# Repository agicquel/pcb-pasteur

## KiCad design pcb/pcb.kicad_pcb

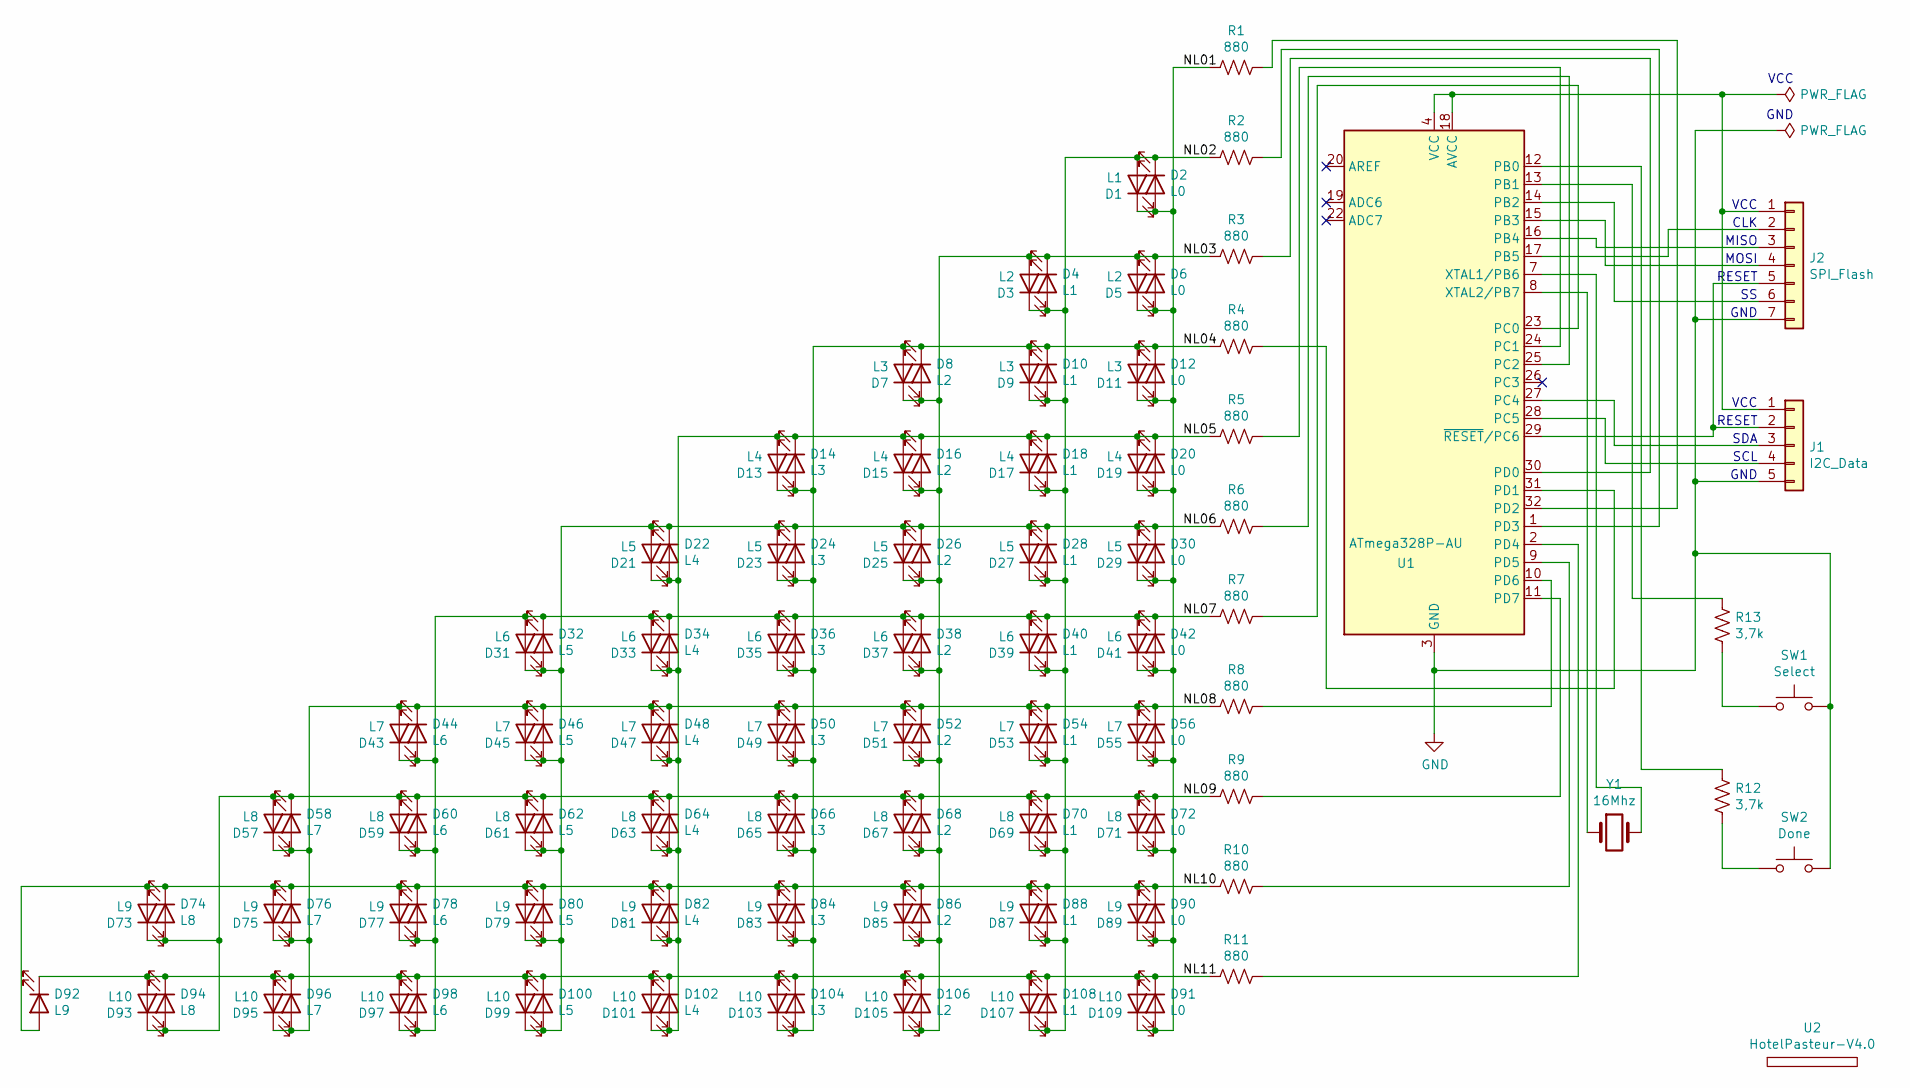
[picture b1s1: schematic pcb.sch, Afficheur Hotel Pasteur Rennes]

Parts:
D1, D4, D10, D18, D28, D40, D54, D70, D88, D108: L1; LED_0603_1608Metric_smallfont
D2, D6, D12, D20, D30, D42, D56, D72, D90, D91: L0; LED_0603_1608Metric_smallfont
D3, D5, D8, D16, D26, D38, D52, D68, D86, D106: L2; LED_0603_1608Metric_smallfont
D7, D9, D11, D14, D24, D36, D50, D66, D84, D104: L3; LED_0603_1608Metric_smallfont
D13, D15, D17, D19, D22, D34, D48, D64, D82, D102: L4; LED_0603_1608Metric_smallfont
D21, D23, D25, D27, D29, D32, D46, D62, D80, D100: L5; LED_0603_1608Metric_smallfont
D31, D33, D35, D37, D39, D41, D44, D60, D78, D98: L6; LED_0603_1608Metric_smallfont
D43, D45, D47, D49, D51, D53, D55, D58, D76, D96: L7; LED_0603_1608Metric_smallfont
D57, D59, D61, D63, D65, D67, D69, D71, D74, D94: L8; LED_0603_1608Metric_smallfont
D73, D75, D77, D79, D81, D83, D85, D87, D89, D92: L9; LED_0603_1608Metric_smallfont
D93, D95, D97, D99, D101, D103, D105, D107, D109: L10; LED_0603_1608Metric_smallfont
J1: I2C_Data; PinSocket_1x05_P2.54mm_Vertical_smallfont
J2: SPI_Flash; PinSocket_1x07_P2.00mm_Horizontal_smallfont
R1, R2, R3, R4, R5, R6, R7, R8, R9, R10, R11: 880; R_0603_1608Metric_smallfont
R12, R13: 3,7k; R_0603_1608Metric_smallfont
SW1: Select; SW_Push_1P1T_NO_6x6mm_H9.5mm_smallfont
SW2: Done; SW_Push_1P1T_NO_6x6mm_H9.5mm_smallfont
U1: ATmega328P-AU; TQFP-32_7x7mm_P0.8mm
U2: HotelPasteur-V4.0; DessinAfficheurV4.0
Y1: 16Mhz; Crystal_SMD_0603-2Pin_6.0x3.5mm_smallfont

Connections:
/NL01: D1.1 (K), D2.2 (A), D5.1 (K), D6.2 (A), D11.1 (K), D12.2 (A), D19.1 (K), D20.2 (A), D29.1 (K), D30.2 (A), D41.1 (K), D42.2 (A), D55.1 (K), D56.2 (A), D71.1 (K), D72.2 (A), D89.1 (K), D90.2 (A), D91.2 (A), D109.1 (K), R1.2
/NL02: D1.2 (A), D2.1 (K), D3.1 (K), D4.2 (A), D9.1 (K), D10.2 (A), D17.1 (K), D18.2 (A), D27.1 (K), D28.2 (A), D39.1 (K), D40.2 (A), D53.1 (K), D54.2 (A), D69.1 (K), D70.2 (A), D87.1 (K), D88.2 (A), D107.1 (K), D108.2 (A), R2.2
/NL03: D3.2 (A), D4.1 (K), D5.2 (A), D6.1 (K), D7.1 (K), D8.2 (A), D15.1 (K), D16.2 (A), D25.1 (K), D26.2 (A), D37.1 (K), D38.2 (A), D51.1 (K), D52.2 (A), D67.1 (K), D68.2 (A), D85.1 (K), D86.2 (A), D105.1 (K), D106.2 (A), R3.2
/NL04: D7.2 (A), D8.1 (K), D9.2 (A), D10.1 (K), D11.2 (A), D12.1 (K), D13.1 (K), D14.2 (A), D23.1 (K), D24.2 (A), D35.1 (K), D36.2 (A), D49.1 (K), D50.2 (A), D65.1 (K), D66.2 (A), D83.1 (K), D84.2 (A), D103.1 (K), D104.2 (A), R4.2
/NL05: D13.2 (A), D14.1 (K), D15.2 (A), D16.1 (K), D17.2 (A), D18.1 (K), D19.2 (A), D20.1 (K), D21.1 (K), D22.2 (A), D33.1 (K), D34.2 (A), D47.1 (K), D48.2 (A), D63.1 (K), D64.2 (A), D81.1 (K), D82.2 (A), D101.1 (K), D102.2 (A), R5.2
/NL06: D21.2 (A), D22.1 (K), D23.2 (A), D24.1 (K), D25.2 (A), D26.1 (K), D27.2 (A), D28.1 (K), D29.2 (A), D30.1 (K), D31.1 (K), D32.2 (A), D45.1 (K), D46.2 (A), D61.1 (K), D62.2 (A), D79.1 (K), D80.2 (A), D99.1 (K), D100.2 (A), R6.2
/NL07: D31.2 (A), D32.1 (K), D33.2 (A), D34.1 (K), D35.2 (A), D36.1 (K), D37.2 (A), D38.1 (K), D39.2 (A), D40.1 (K), D41.2 (A), D42.1 (K), D43.1 (K), D44.2 (A), D59.1 (K), D60.2 (A), D77.1 (K), D78.2 (A), D97.1 (K), D98.2 (A), R7.2
/NL08: D43.2 (A), D44.1 (K), D45.2 (A), D46.1 (K), D47.2 (A), D48.1 (K), D49.2 (A), D50.1 (K), D51.2 (A), D52.1 (K), D53.2 (A), D54.1 (K), D55.2 (A), D56.1 (K), D57.1 (K), D58.2 (A), D75.1 (K), D76.2 (A), D95.1 (K), D96.2 (A), R8.2
/NL09: D57.2 (A), D58.1 (K), D59.2 (A), D60.1 (K), D61.2 (A), D62.1 (K), D63.2 (A), D64.1 (K), D65.2 (A), D66.1 (K), D67.2 (A), D68.1 (K), D69.2 (A), D70.1 (K), D71.2 (A), D72.1 (K), D73.1 (K), D74.2 (A), D93.1 (K), D94.2 (A), R9.2
/NL10: D73.2 (A), D74.1 (K), D75.2 (A), D76.1 (K), D77.2 (A), D78.1 (K), D79.2 (A), D80.1 (K), D81.2 (A), D82.1 (K), D83.2 (A), D84.1 (K), D85.2 (A), D86.1 (K), D87.2 (A), D88.1 (K), D89.2 (A), D90.1 (K), D92.2 (A), R10.2
/NL11: D91.1 (K), D92.1 (K), D93.2 (A), D94.1 (K), D95.2 (A), D96.1 (K), D97.2 (A), D98.1 (K), D99.2 (A), D100.1 (K), D101.2 (A), D102.1 (K), D103.2 (A), D104.1 (K), D105.2 (A), D106.1 (K), D107.2 (A), D108.1 (K), D109.2 (A), R11.2
GND: J1.5, J2.7, SW1.2, SW2.2, U1.3 (GND), U1.5 (GND), U1.21 (GND)
unnamed: J1.1, J2.1, U1.4 (VCC), U1.6 (VCC), U1.18 (AVCC)
unnamed: J1.2, J2.5, U1.29 (~RESET~/PC6)
unnamed: J1.3, U1.27 (PC4)
unnamed: J1.4, U1.28 (PC5)
unnamed: J2.2, U1.17 (PB5)
unnamed: J2.3, U1.16 (PB4)
unnamed: J2.4, U1.15 (PB3)
unnamed: J2.6, U1.14 (PB2)
unnamed: R1.1, U1.32 (PD2)
unnamed: R2.1, U1.1 (PD3)
unnamed: R3.1, U1.30 (PD0)
unnamed: R4.1, U1.31 (PD1)
unnamed: R5.1, U1.24 (PC1)
unnamed: R6.1, U1.25 (PC2)
unnamed: R7.1, U1.23 (PC0)
unnamed: R8.1, U1.10 (PD6)
unnamed: R9.1, U1.11 (PD7)
unnamed: R10.1, U1.9 (PD5)
unnamed: R11.1, U1.2 (PD4)
unnamed: R12.1, U1.12 (PB0)
unnamed: R12.2, SW2.1
unnamed: R13.1, U1.13 (PB1)
unnamed: R13.2, SW1.1
unnamed: U1.7 (XTAL1/PB6), Y1.2
unnamed: U1.8 (XTAL2/PB7), Y1.1

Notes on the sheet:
VCC
GND
CLK
MISO
MOSI
RESET
SDA
SCL

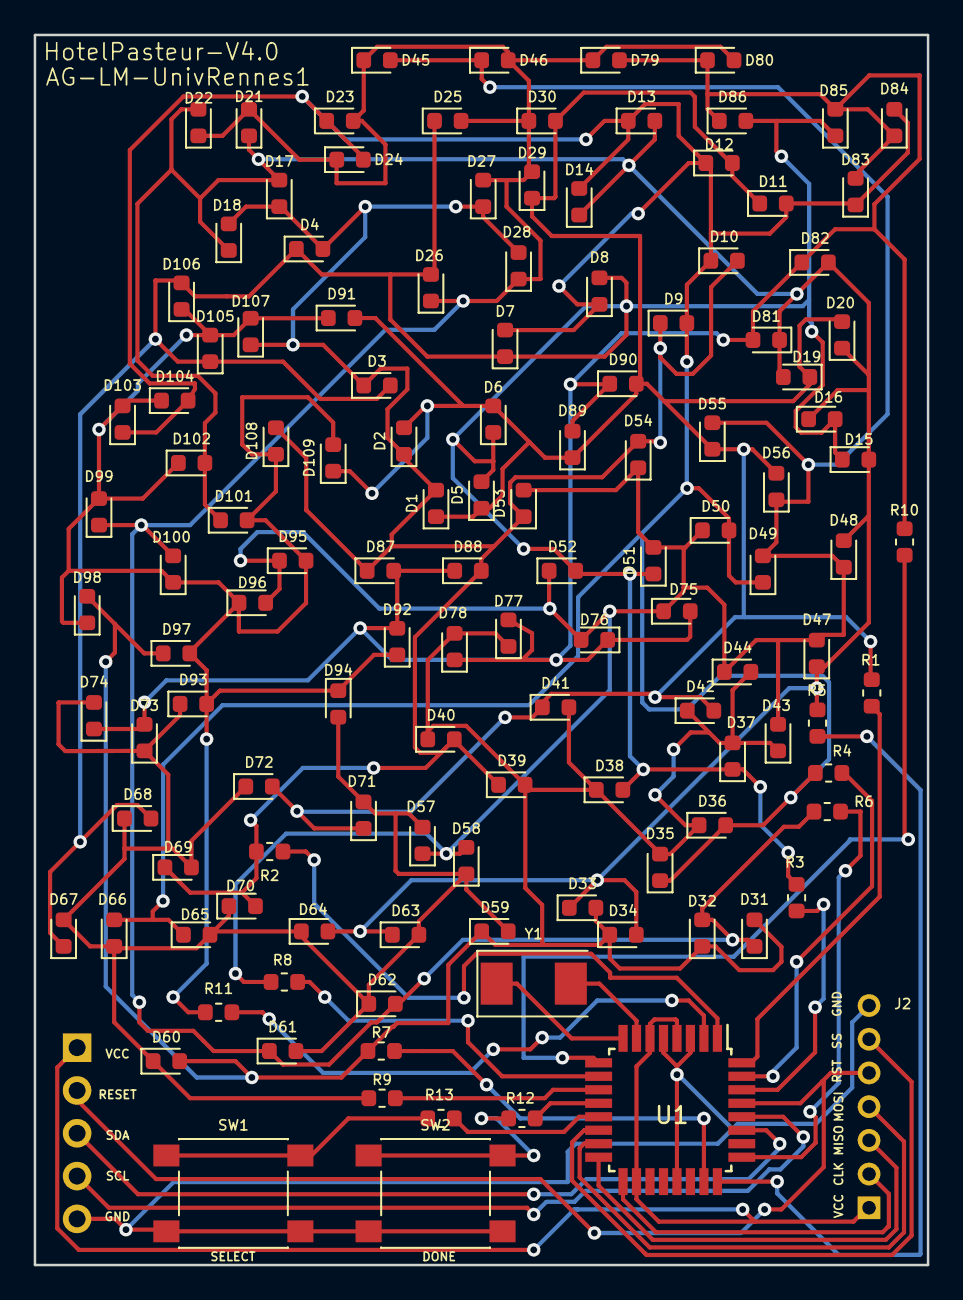
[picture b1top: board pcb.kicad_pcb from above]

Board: 2 copper layers, 53.0 x 73.0 mm, 129 parts (1 on the bottom side), 37 nets.

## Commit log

2020-06-10 debut du sch
2020-06-10 add switch footprint
2020-06-11 add pcb leds
2020-06-11 fix i2c label
2020-06-11 put all components on the board
2020-06-11 fix gnd of i2c
2020-06-15 led placement
2020-06-15 led placement fixed
2020-06-16 routing v1
2020-06-16 add crystal to the pcb
2020-06-16 reverse orientation spi / i2c
2020-06-17 v2 with bom
2020-06-17 clean footprints and update bom
2020-06-18 add label and netlist parser
2020-06-18 Minor fix and prepare for release
2020-06-18 Add assembly files and fix silk details
2020-06-18 Update Library
2020-06-18 Fix LED naming and parsing script for SMD components
2020-07-10 change order the of generated table
2020-07-31 fix buttons gnd
